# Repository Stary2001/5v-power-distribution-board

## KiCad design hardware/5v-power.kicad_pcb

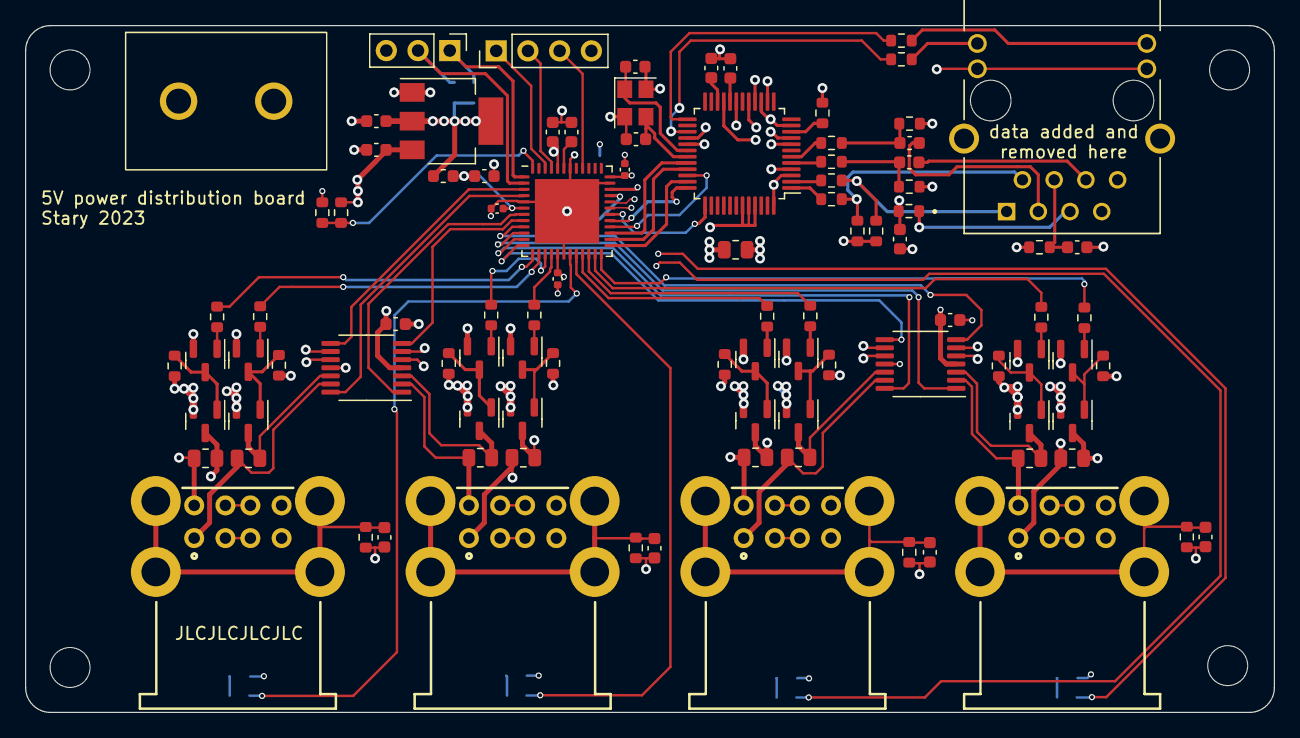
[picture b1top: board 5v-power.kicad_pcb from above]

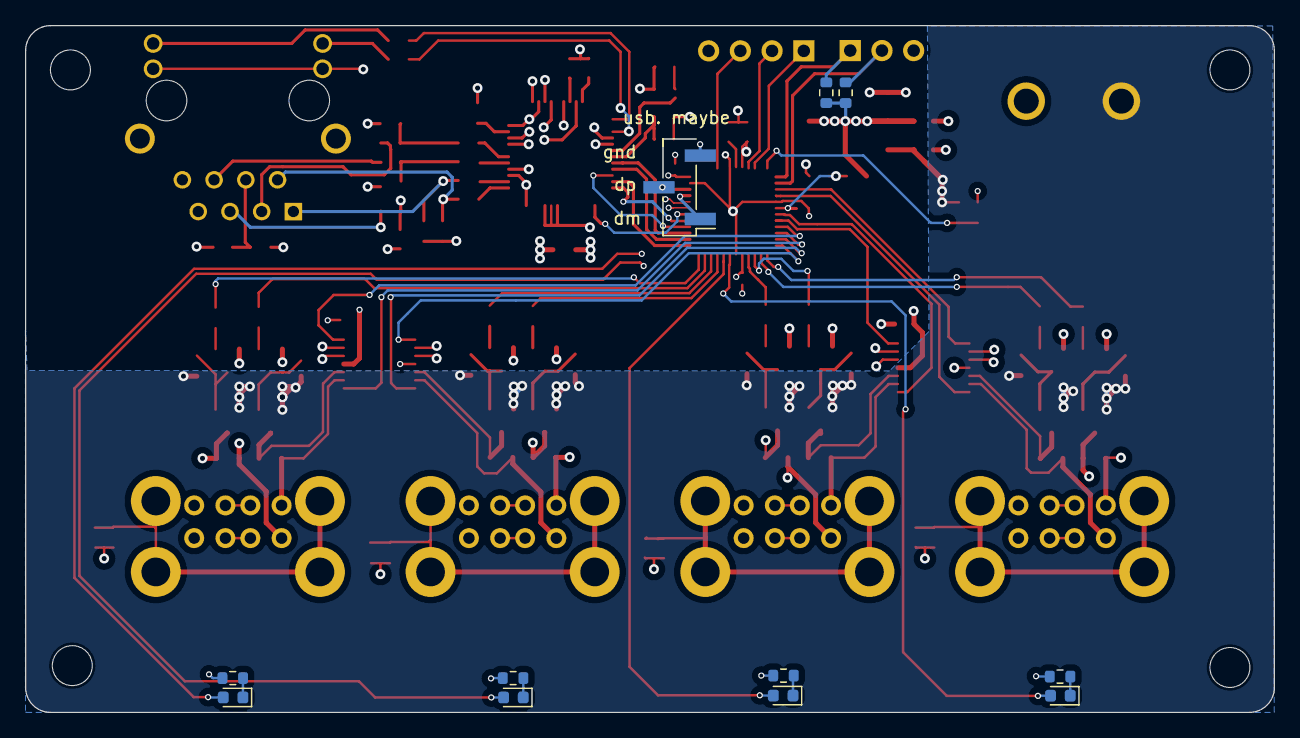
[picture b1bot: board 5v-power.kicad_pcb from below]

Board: 4 copper layers, 100.0 x 55.0 mm, 112 parts (11 on the bottom side), 110 nets.

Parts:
C1, C5, C6, C7, C8, C9, C19: 100n; C_0603_1608Metric
C2, C3, C17: 10u; C_0603_1608Metric
C4: 26p?; C_0603_1608Metric
C10: 26p; C_0603_1608Metric
C11, C13: 10n; C_0603_1608Metric
C12: 4.7u; C_0603_1608Metric
C14, C15: 6.8n; C_0603_1608Metric
C16: 22n; C_0603_1608Metric
C18, C21, C22: 100n; C_0402_1005Metric
C20: 1u; C_0603_1608Metric
D1, D2, D3, D4: LED_Small; LED_0603_1608Metric
FB1: MH2029-601Y; R_0805_2012Metric
FB2: FerriteBead_Small; L_0603_1608Metric
H1, H2, H3, H4: MountingHole; MountingHole_3.2mm_M3
J1: Conn_01x04; PinHeader_1x04_P2.54mm_Vertical
J2: Screw_Terminal_01x02; Amphenol_YK3210203000G
J3, J4, J5, J6: USB_A_Stacked; GCT_USB1035-XX-X-X-X-B_REVE
J7: RJ45_Abracon_ARJM11D7-009-AB-EW2; ABRACON_ARJM11C7-009-AB-EW2
J8: Conn_01x03_Pin; PinHeader_1x03_P2.54mm_Vertical
J9: Conn_01x03_Pin; PinHeader_1x03_P2.54mm_Vertical_SMD_Pin1Left
Q1, Q2, Q5, Q6, Q9, Q10, Q13, Q14: AO3401A; SOT-23
Q3, Q4, Q7, Q8, Q11, Q12, Q15, Q16: MMBT3904; SOT-23
R1, R2, R10, R12, R15, R17, R22, R24, R29, R31: 10k; R_0603_1608Metric
R3, R4, R8, R9, R19, R20, R26, R27: 5m; R_0805_2012Metric
R5, R6, R46, R47, R48, R49: R_Small; R_0603_1608Metric
R7, R14, R21, R28: 1M; R_0603_1608Metric
R11, R13, R16, R18, R23, R25, R30, R32: 1k; R_0603_1608Metric
R33: 12.4k; R_0603_1608Metric
R34, R35, R36, R37: 33; R_0603_1608Metric
R38, R39, R40, R41: 50; R_0603_1608Metric
R42, R43: 10; R_0603_1608Metric
R44, R45: 330; R_0603_1608Metric
U1: W5500; LQFP-48_7x7mm_P0.5mm
U2, U3: INA4180; TSSOP-14_4.4x5mm_P0.65mm
U4: AMS1117-3.3; SOT-223-3_TabPin2
U5: ATSAMD21G17A-M; QFN-48-1EP_7x7mm_P0.5mm_EP5.15x5.15mm
Y1: RH100-25.000-18-F-1020-EXT-TR; Crystal_SMD_3225-4Pin_3.2x2.5mm

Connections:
+1V8: C20.1, U5.43 (VDDCORE)
+3V3: C2.1, C8.1, C9.1, C19.1, C21.1, C22.1, FB1.1, FB2.2, R47.1, R48.1, U1.28 (VDD), U1.43 (PMODE2), U1.44 (PMODE1), U1.45 (PMODE0), U2.4 (VS), U3.4 (VS), U4.2 (VO), U5.17 (VDDIO), U5.36 (VDDIO), U5.44 (VDDIN)
+5V: C3.1, J2.1, Q1.2 (S), Q2.2 (S), Q5.2 (S), Q6.2 (S), Q9.2 (S), Q10.2 (S), Q13.2 (S), Q14.2 (S), R1.1, R10.1, R12.1, R15.1, R17.1, R22.1, R24.1, R29.1, R31.1, U4.3 (VI)
/Ethernet/actled: R45.2, U1.27 (ACTLED)
/Ethernet/avdd: FB1.2, J7.9, J7.11, R38.1, R39.1, R43.1, U1.4 (AVDD), U1.8 (AVDD), U1.11 (AVDD), U1.15 (AVDD), U1.17 (AVDD), U1.21 (AVDD)
/Ethernet/eth_rxn: C15.1, R36.2, R41.2
/Ethernet/eth_rxp: C14.1, R37.2, R40.2
/Ethernet/eth_txn: J7.2 (TD-), R34.2, R39.2
/Ethernet/eth_txp: J7.1 (TD+), R35.2, R38.2
/Ethernet/linkled: R44.2, U1.25 (LINKLED)
/Vsense: R1.2, R2.1, U5.48 (PB03)
/led1: D1.2 (A), U5.19 (PB10)
/led2: D2.2 (A), U5.20 (PB11)
/led3: D3.2 (A), U5.31 (PA22)
/led4: D4.2 (A), U5.32 (PA23)
/mcu_vddana: C17.1, C18.1, FB2.1, U5.6 (VDDANA)
/mcu_~reset: J1.3, U5.40 (~RESET)
/port1_isense1+: Q1.3 (D), R4.2, U2.10 (IN+3)
/port1_isense1-: J3.1 (VBUS1), R4.1, U2.9 (IN-3)
/port1_isense1_out: U2.14 (OUT4), U5.4 (PA03)
/port1_isense2+: Q2.3 (D), R8.2, U2.12 (IN+4)
/port1_isense2-: J3.5 (VBUS2), R8.1, U2.13 (IN-4)
/port1_isense2_out: U2.8 (OUT3), U5.3 (PA02)
/port1_switch_1: R11.1, U5.13 (PA08)
/port1_switch_2: R13.1, U5.14 (PA09)
/port2_isense1+: Q5.3 (D), R3.2, U2.3 (IN+1)
/port2_isense1-: J4.1 (VBUS1), R3.1, U2.2 (IN-1)
/port2_isense1_out: U2.7 (OUT2), U5.8 (PB09)
/port2_isense2+: Q6.3 (D), R9.2, U2.5 (IN+2)
/port2_isense2-: J4.5 (VBUS2), R9.1, U2.6 (IN-2)
/port2_isense2_out: U2.1 (OUT1), U5.7 (PB08)
/port2_switch_1: R16.1, U5.15 (PA10)
/port2_switch_2: R18.1, U5.16 (PA11)
/port3_isense1+: Q9.3 (D), R19.2, U3.10 (IN+3)
/port3_isense1-: J5.1 (VBUS1), R19.1, U3.9 (IN-3)
/port3_isense1_out: U3.14 (OUT4), U5.11 (PA06)
/port3_isense2+: Q10.3 (D), R20.2, U3.12 (IN+4)
/port3_isense2-: J5.5 (VBUS2), R20.1, U3.13 (IN-4)
/port3_isense2_out: U3.8 (OUT3), U5.12 (PA07)
/port3_switch_1: R23.1, U5.21 (PA12)
/port3_switch_2: R25.1, U5.22 (PA13)
/port4_isense1+: Q13.3 (D), R26.2, U3.3 (IN+1)
/port4_isense1-: J6.1 (VBUS1), R26.1, U3.2 (IN-1)
/port4_isense1_out: U3.7 (OUT2), U5.9 (PA04)
/port4_isense2+: Q14.3 (D), R27.2, U3.5 (IN+2)
/port4_isense2-: J6.5 (VBUS2), R27.1, U3.6 (IN-2)
/port4_isense2_out: U3.1 (OUT1), U5.10 (PA05)
/port4_switch_1: R30.1, U5.23 (PA14)
/port4_switch_2: R32.1, U5.24 (PA15)
/swclk: J1.2, U5.45 (PA30)
/swdio: J1.1, U5.46 (PA31)
GND: C1.2, C2.2, C3.2, C4.2, C5.2, C6.2, C7.2, C8.2, C9.2, C10.2, C11.2, C12.2, C13.2, C16.2, C17.2, C18.2, C19.2, C20.2, C21.2, C22.2, J1.4, J2.2, J3.4 (GND1), J3.8 (GND2), J4.4 (GND1), J4.8 (GND2), J5.4 (GND1), J5.8 (GND2), J6.4 (GND1), J6.8 (GND2), J7.8, J7.SH, J8.3, J9.3, Q3.2 (E), Q4.2 (E), Q7.2 (E), Q8.2 (E), Q11.2 (E), Q12.2 (E), Q15.2 (E), Q16.2 (E), R2.2, R5.2, R6.2, R7.2, R14.2, R21.2, R28.2, R33.2, R46.2, R49.2, U1.3 (AGND), U1.9 (AGND), U1.14 (AGND), U1.16 (AGND), U1.19 (AGND), U1.29 (GND), U1.48 (AGND), U2.11 (GND), U3.11 (GND), U4.1 (GND), U5.5 (GNDANA), U5.18 (GND), U5.35 (GND), U5.42 (GND), U5.49 (EP), Y1.2, Y1.4
unnamed: C13.1, R40.1, R41.1, R42.1
unnamed: D1.1 (K), R5.1
unnamed: D2.1 (K), R6.1
unnamed: D3.1 (K), R46.1
unnamed: D4.1 (K), R49.1
unnamed: J3.2 (D1-), J3.3 (D1+)
unnamed: J3.6 (D2-), J3.7 (D2+)
unnamed: C5.1, J3.9 (Shield), R7.1
unnamed: J4.2 (D1-), J4.3 (D1+)
unnamed: J4.6 (D2-), J4.7 (D2+)
unnamed: C1.1, J4.9 (Shield), R14.1
unnamed: J5.2 (D1-), J5.3 (D1+)
unnamed: J5.6 (D2-), J5.7 (D2+)
unnamed: C6.1, J5.9 (Shield), R21.1
unnamed: J6.2 (D1-), J6.3 (D1+)
unnamed: J6.6 (D2-), J6.7 (D2+)
unnamed: C7.1, J6.9 (Shield), R28.1
unnamed: J7.10, R44.1
unnamed: J7.12, R45.1
unnamed: J7.5 (RCT), R42.2
unnamed: C14.2, J7.3 (RD+)
unnamed: C15.2, J7.6 (RD-)
unnamed: C16.1, J7.4 (TCT), R43.2
unnamed: J8.1, R47.2, U5.1 (PA00)
unnamed: J8.2, R48.2, U5.2 (PA01)
unnamed: J9.1, U5.33 (PA24)
unnamed: J9.2, U5.34 (PA25)
unnamed: Q1.1 (G), Q3.3 (C), R10.2
unnamed: Q2.1 (G), Q4.3 (C), R12.2
unnamed: Q3.1 (B), R11.2
unnamed: Q4.1 (B), R13.2
unnamed: Q5.1 (G), Q7.3 (C), R15.2
unnamed: Q6.1 (G), Q8.3 (C), R17.2
unnamed: Q7.1 (B), R16.2
unnamed: Q8.1 (B), R18.2
unnamed: Q10.1 (G), Q12.3 (C), R24.2
unnamed: Q11.1 (B), R23.2
unnamed: Q9.1 (G), Q11.3 (C), R22.2
unnamed: Q12.1 (B), R25.2
unnamed: Q13.1 (G), Q15.3 (C), R29.2
unnamed: Q14.1 (G), Q16.3 (C), R31.2
unnamed: Q15.1 (B), R30.2
unnamed: Q16.1 (B), R32.2
unnamed: C11.1, U1.22 (1V2O)
unnamed: R33.1, U1.10 (EXRES1)
unnamed: R36.1, U1.5 (RXN)
unnamed: R37.1, U1.6 (RXP)
unnamed: C12.1, U1.20 (TOCAP)
unnamed: R34.1, U1.1 (TXN)
unnamed: R35.1, U1.2 (TXP)
unnamed: C4.1, U1.30 (XI/CLKIN), Y1.1
unnamed: C10.1, U1.31 (XO), Y1.3
eth_clk: U1.33 (SCLK), U5.26 (PA17)
eth_miso: U1.34 (MISO), U5.28 (PA19)
eth_mosi: U1.35 (MOSI), U5.25 (PA16)
eth_~cs: U1.32 (~SCS), U5.27 (PA18)
eth_~int: U1.36 (~INT), U5.29 (PA20)
eth_~rst: U1.37 (~RST), U5.30 (PA21)

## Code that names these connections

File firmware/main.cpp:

#include <stdio.h>
#include "sam/heap.h"
#include "sam/gpio.h"
#include "sam/bod.h"
#include "sam/clock.h"
#include "sam/sercom_usart.h"
#include "sam/pinmux.h"
#include "sam/serial_number.h"
#include "sam/adc.h"
#include "mongoose_integration.h"

/* pa00-01 are i2c */
/* pa02 - pa08, pb08,09 are isense */
/* pb03 is vsense */
/* pa8-15 are the switches */
/* pa16-pa21 are ethernet spi+int/rst */
/* pa22 is led3 */
/* pa24,25 are usb ofc */

const unsigned int PORT1_ISENSE_A = 2;
const unsigned int PORT1_ISENSE_B = 3;
const unsigned int PORT2_ISENSE_A = 8; // port b
const unsigned int PORT2_ISENSE_B = 9; // port b
const unsigned int PORT3_ISENSE_A = 6;
const unsigned int PORT3_ISENSE_B = 7;
const unsigned int PORT4_ISENSE_A = 4;
const unsigned int PORT4_ISENSE_B = 5;

const unsigned int PORT1_ENABLE_A = 8;
const unsigned int PORT1_ENABLE_B = 9;
const unsigned int PORT2_ENABLE_A = 10;
const unsigned int PORT2_ENABLE_B = 11;
const unsigned int PORT3_ENABLE_A = 12;
const unsigned int PORT3_ENABLE_B = 13;
const unsigned int PORT4_ENABLE_A = 14;
const unsigned int PORT4_ENABLE_B = 15;


const unsigned int LED1 = 10; // port b
const unsigned int LED2 = 11; // port b
const unsigned int LED3 = 22; // port a
const unsigned int LED4 = 23; // porta

const unsigned int port_gpios[] = {
	PORT1_ENABLE_A,
	PORT1_ENABLE_B,
	PORT2_ENABLE_A,
	PORT2_ENABLE_B,
	PORT3_ENABLE_A,
	PORT3_ENABLE_B,
	PORT4_ENABLE_A,
	PORT4_ENABLE_B
};

struct port { unsigned int port; unsigned int num; };
const struct port port_adcs[] = {
	{PORT_A, PORT1_ISENSE_A},
	{PORT_A, PORT1_ISENSE_B},
	{PORT_B, PORT2_ISENSE_A},
	{PORT_B, PORT2_ISENSE_B},
	{PORT_B, PORT3_ISENSE_A},
	{PORT_B, PORT3_ISENSE_B},
	{PORT_B, PORT4_ISENSE_A},
	{PORT_B, PORT4_ISENSE_B},
};

extern uint64_t __gtod_millis;
uint64_t system_ticks = 0;
bool value = true;
extern "C" void SysTick_Handler (void)
{
	system_ticks++;
	__gtod_millis = system_ticks;
}

char fake_heap[4096 * 3 - 800];

int main() {
	__init_heap(fake_heap, sizeof(fake_heap));

	clock_switch_to_8mhz();
	bod_init();
	bod_set_3v3();

	clock_switch_to_48mhz_from_usb();
	clock_setup_gclk2_8mhz();

	clock_setup_systick_1ms();

	for(unsigned int i = 0; i < 8; i++) {
		port_set_value(PORT_A, port_gpios[i], false);
		port_set_direction(PORT_A, port_gpios[i], true);

		port_set_function(port_adcs[i].port, port_adcs[i].num, 1);
		port_set_pmux_enable(port_adcs[i].port, port_adcs[i].num, true);
	}

	port_set_direction(PORT_B, LED1, true);
	port_set_value(PORT_B, LED1, true);

	port_set_direction(PORT_B, LED2, true);
	port_set_value(PORT_B, LED2, true);

	port_set_direction(PORT_A, LED3, true);
	port_set_value(PORT_A, LED3, true);

	port_set_direction(PORT_A, LED4, true);
	port_set_value(PORT_A, LED4, true);

	// sercom setup
	port_set_function(PORT_A, 0, 3);
	port_set_function(PORT_A, 1, 3);
	port_set_pmux_enable(PORT_A, 0, true);
	port_set_pmux_enable(PORT_A, 1, true);

	// enable port1 a
	port_set_value(PORT_A, PORT1_ENABLE_A, true);
	port_set_value(PORT_A, PORT1_ENABLE_B, true);

	SercomUart<1> sercom;
	sercom.init(0, 1); // sercom[0] used for tx, sercom[1] used for rx

	ADCClass adc;
	adc.init(4, 1);
	adc.select(0);

	ethernet_init();

	uint32_t last_system_tick = 0;
	while(true) {
		ethernet_tick();

		if((system_ticks % 100) == 0 && system_ticks != last_system_tick) {
			last_system_tick = system_ticks;
		}
	}

	return 0;
}

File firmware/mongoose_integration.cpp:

#include "mongoose.h"
#include "sam/sercom_spi.h"


#include "sam/gpio.h"
#include "sam/pinmux.h"
#include "sam/serial_number.h"
#include "mongoose_integration.h"


// http://9net.org/screenshots/1709135387.png
// ethernet

const int ETH_MOSI = 16;
const int ETH_CLK = 17;
const int ETH_CS = 18;
const int ETH_MISO = 19;
const int ETH_INT = 21;
const int ETH_RST = 21;

SercomSPI<3> sercom_spi;
struct mg_mgr mgr;  // Mongoose event manager

struct mg_tcpip_spi spi = {
	NULL,                                               // SPI data
	[](void *) { port_set_value(PORT_A, ETH_CS, false); },          // begin transation
	[](void *) { port_set_value(PORT_A, ETH_CS, true); },         // end transaction
	[](void * data, uint8_t c) { sercom_spi.send_byte(c); return sercom_spi.read_byte(); },  // execute transaction
};

struct mg_tcpip_if mif = {
	.mac = {2, 0, 1, 2, 3, 5},
	.driver = &mg_tcpip_driver_w5500,
	.driver_data = &spi
};  // network interface

const char *index_html = "<!doctype html>"
"<html>"
"<head>"
"<title>Power</title>"
"<style> #control { max-width: 30%; display: grid;  grid-template-columns: 1fr 1fr 1fr 1fr; grid-template-rows: 1fr 1fr;} .port { border: 1px black;} .port-stats { } </style>"
"</head>"
"<body>"
"<div id='control'>"
"<div class='port'><div class='port-stats'>Stats stats</div><button onclick='toggle(1)'>1</button></div>"
"<div class='port'><div class='port-stats'>Stats stats</div><button onclick='toggle(2)'>2</button></div>"
"<div class='port'><div class='port-stats'>Stats stats</div><button onclick='toggle(3)'>3</button></div>"
"<div class='port'><div class='port-stats'>Stats stats</div><button onclick='toggle(4)'>4</button></div>"
"<div class='port'><button onclick='toggle(5)'>5</button><div class='port-stats'>Stats stats</div></div>"
"<div class='port'><button onclick='toggle(6)'>6</button><div class='port-stats'>Stats stats</div></div>"
"<div class='port'><button onclick='toggle(7)'>7</button><div class='port-stats'>Stats stats</div></div>"
"<div class='port'><button onclick='toggle(8)'>8</button><div class='port-stats'>Stats stats</div></div>"
"</div>"
"</body>"
"<script>"
"function toggle(i) { ws.send('toggle ' + i.toString()); }"
"var ws;"
"ws = new WebSocket('ws://' + location.host + '/websocket');"
"ws.onopen = function() { ws.send('ping'); };"
"ws.onmessage = function(ev) { console.log(ev.data); }"
"</script>"
"</html>";

struct mg_connection *websocket_conn = nullptr;

static void http_event_callback(struct mg_connection *c, int ev, void *ev_data) {
  if (ev == MG_EV_HTTP_MSG) {
    struct mg_http_message *hm = (struct mg_http_message *) ev_data;
    if (mg_http_match_uri(hm, "/websocket")) {
		websocket_conn = c;
    	mg_ws_upgrade(c, hm, NULL);
    } else if (mg_http_match_uri(hm, "/") || mg_http_match_uri(hm, "/index.html")) {
	  mg_http_reply(c, 200, "", "%s", index_html);
    } else {
		mg_http_reply(c, 404, "", "Not found!");
	}
  } else if (ev == MG_EV_WS_MSG) {
    struct mg_ws_message *wm = (struct mg_ws_message *) ev_data;
    mg_ws_send(c, "ok", 2, WEBSOCKET_OP_TEXT);
	printf("websocket message: '%.*s'\r\n", wm->data.len, wm->data.ptr);
  } else if(ev == MG_EV_WS_CTL) {
	struct mg_ws_message *wm = (struct mg_ws_message *) ev_data;
	uint8_t op = wm->flags & 15;
	if(op == WEBSOCKET_OP_CLOSE && c == websocket_conn) {
		printf("websocket closed\r\n");
		websocket_conn = nullptr;
	}
  }
}

int counter = 0;
void ethernet_init() {
	port_set_value(PORT_A, ETH_CS, true);
	port_set_direction(PORT_A, ETH_CS, true);

	port_set_direction(PORT_A, ETH_INT, false);
	port_set_direction(PORT_A, ETH_RST, true);
	port_set_value(PORT_A, ETH_RST, true);

	port_set_function(PORT_A, ETH_CLK, 3); // sercom alt, sercom 3
	port_set_function(PORT_A, ETH_MISO, 3);
	port_set_function(PORT_A, ETH_MOSI, 3);
	port_set_pmux_enable(PORT_A, ETH_CLK, true);
	port_set_pmux_enable(PORT_A, ETH_MISO, true);
	port_set_pmux_enable(PORT_A, ETH_MOSI, true);

	port_set_value(PORT_A, ETH_RST, false);
	// sleep
	for(volatile int i = 0; i < 1000000; i++) {}
	port_set_value(PORT_A, ETH_RST, true);
	// sleep
	for(volatile int i = 0; i < 1000000; i++) {}

	sercom_spi.init(3, 0, 1000000);
	mg_mgr_init(&mgr);
	mg_log_set(MG_LL_DEBUG);
	mg_tcpip_init(&mgr, &mif);

	// Start a 5 sec timer, print status message periodically
	mg_timer_add(
		&mgr, 5000, MG_TIMER_REPEAT,
		[](void *) {
			if(websocket_conn != nullptr) {
				char buff[64]; 
				size_t len = sprintf(buff, "ping %i\n", counter++);
				mg_ws_send(websocket_conn, buff, len, WEBSOCKET_OP_TEXT);
			} else {
				printf("No websocket!\r\n");
			}
			MG_INFO(("ethernet: %s", mg_tcpip_driver_w5500.up(&mif) ? "up" : "down"));
		},
		NULL);

    mg_http_listen(&mgr, "http://0.0.0.0", http_event_callback, &mgr);
}

void ethernet_tick() {
    mg_mgr_poll(&mgr, 1);
}

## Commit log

2024-01-17 Initial commit - hardware v1 as manufactured
2024-01-17 Firmware as of now
2024-02-28 rev2
2024-02-28 add new source, maybe
2024-02-28 add submodule
2024-03-01 ethernet
2024-04-14 mongoose??
2024-04-21 mongoose real
